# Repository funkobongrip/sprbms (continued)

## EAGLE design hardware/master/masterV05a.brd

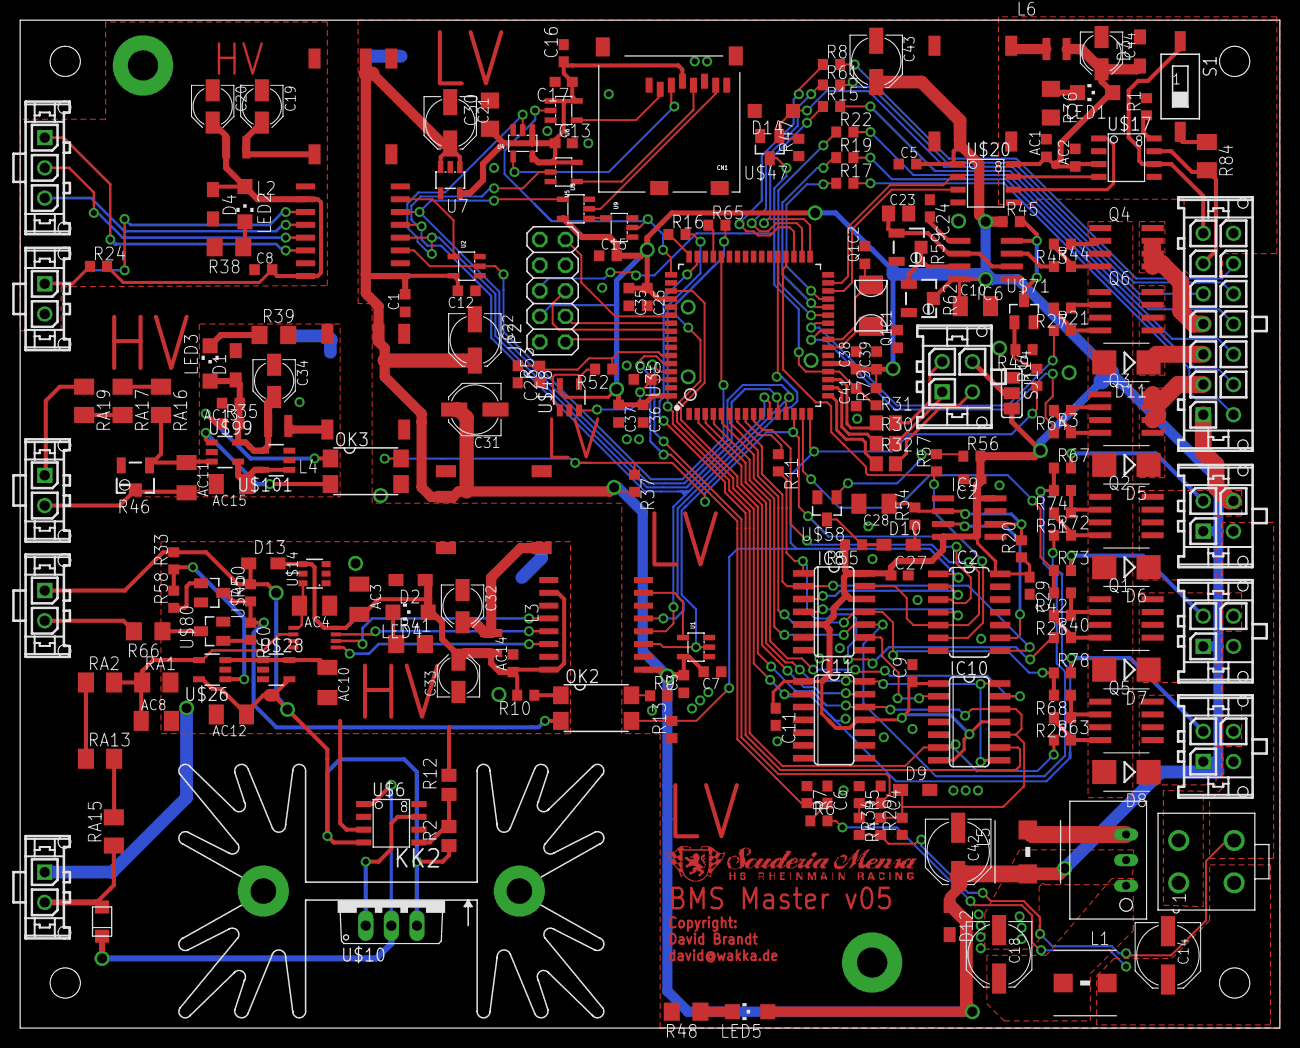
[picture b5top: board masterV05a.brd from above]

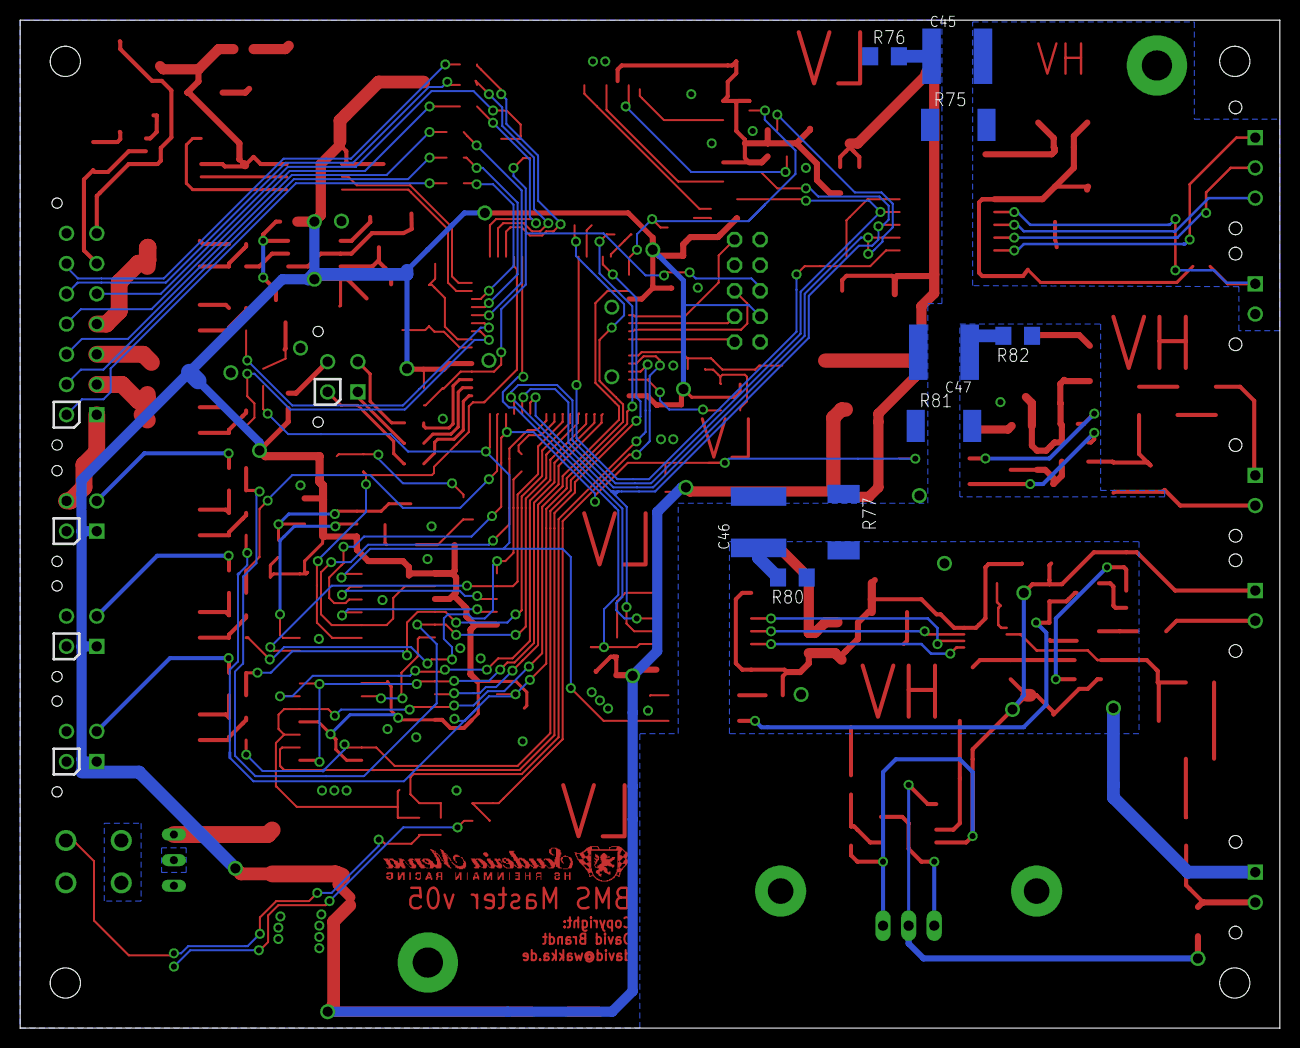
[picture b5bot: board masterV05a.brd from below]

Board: 2 copper layers, 125.0 x 100.0 mm, 234 parts (9 on the bottom side), 162 nets.

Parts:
AC1, AC2, AC13, AC14: 100n; C0603K
AC3: 1u; C1206K
AC4, AC8, AC10, AC11, AC12, AC15: 10u; C1206K
C1, C3, C5, C7, C8, C12, C15, C25, C36, C38, C41: 100n; C0603K
C2, C4, C6, C9, C11, C26, C27, C29: 1u; C0603
C10: 10u; C1206K
C13, C16, C17: 100n; C0603
C14, C18: 22u50v; PANASONIC_D
C19, C20, C32, C33, C34, C44: 10u16V; PANASONIC_B
C21, C22, C31, C43: 33u10V; PANASONIC_C
C23: 1u; C0805K
C24: 10n; C0603
C28: 2.2u; C1206K
C30: 10u; C1206
C35, C37, C39, C40: 1u; C0603K
C42: 150u10v; PANASONIC_D
C45: DNP; C2220K
C46, C47: C2220K
CN1: MICROSD
D1, D2, D3, D4, D12: 5.5; SOD323-W
D5, D6, D7, D8, D11: SMB
D9: 5.1; SOD323-W
D10, D13: SOD323-W
D14: 20V; SOD123
D15: RS07J; DO-219AB
DC2, DC3, DC4, DC5: TES 1-0511; ISF
IC2: 74AC04D; SO14
IC6, IC9: NE555D; SO08
IC8: 4082D; SO14
IC10, IC11: 74AC11074D; SO14
JP2: 2X05
KK2: SK129-PAD; SK129
L1, L5: 7447786008; WE-PD_6033/6050_PLASTIC_BASE
L2, L3, L4, L6: 74479887310; WE-PMI_1008
LED1, LED2, LED3, LED4, LED5: 1318255; CHIPLED_1206
OK2, OK3: LTV816S; SMD4
Q1, Q2, Q3, Q4, Q5, Q6: SO-08
Q1C1, Q1C2: 18pf; C0603K
R1: 1.5k; R0603
R2, R12: R0805
R3, R21, R40, R44, R63, R72: 10; R0603
R4, R6: 4.7k; R0603
R5, R7: 680; R0603
R8, R15, R17, R19, R22, R24, R42, R45, R52, R57, R58, R60, R61, R68: 1k; R0603
R9, R47, R54, R67, R73, R78: 100; R0603
R10, R35: 330; R0603
R11, R16, R20, R49, R55, R56, R65: 100k; R0603
R13, R14, R29, R33, R34, R37, R50, R74, R79: 10k; R0603
R26, R27, R28, R43, R51, R64: 470; R0603
R30, R31, R32: 220; R0805
R36, R38, R39, R41, R48: 140; R1206
R46: 100k; 3223W
R53: NTC1k; R0603
R59: 500k; 3223W
R62: 5k; 3223W
R66: 470; R1206
R75: DNP; R2512
R76: DNP; R1206
R77, R81: R2512
R80, R82: R1206
R84: 120; M1206
RA1: 10k; M1206
RA2, RA13, RA15, RA16, RA17, RA19: 330k; M1206
S1: SWS001; SMS-001
SJ1: SJ_2
U1, U2, U9: SOT23-5
U3: AT90CAN128-16AI; TQFP64-0.8MM
U4, U5, U6, U8: SN74AHC1G126DBVR; SOT23-5
U7: LP2985-33DBVR; SOT23-DBV
U$6: LR645; SO-8
U$9: ADUM1401; SO16WB
U$10: DN2540TO220; TO220V
U$11: ADUM1301; SO16WB
U$14: LT6656; SOT23-6
U$16: LTC1864; MS8
U$17: MCP2551; SO-8
U$20: ADUM1201; SO-8
U$26, U$99: LT1716; SOT23-5
U$28, U$101: LT6650; SOT23-5
U$45, U$47, U$58, U$71, U$80: 2N7002; SOT23
U$48: LT1782; SOT23-5
U$50: TSR1
U$1000: SMLOGOS
X1, X2, X9, X13: 43650-0215
X3: 43045-1412
X4, X5, X6, X8: 43045-0412
X7: 43650-0315
X10: MINI-FIT-JR-045566; 5566-04
Y1: 16Mhz; CX-53G

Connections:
40VOUT: OK2.2, R50.1, R60.1, U$45.3
!40VCOUT: R66.1, U$80.3
!40VCOUTW: R33.1, R58.2, U$26.1
!ANDOUT2: D10.C, R55.1, U$58.3
!CSADC: U1.2, U3.37, U$11.P$3
!CSLT: U2.2, U3.44, U$9.P$3
!PRECH_C: IC2.3, OK3.4, R37.1, U3.14
!RELAI+_C: IC2.6, R57.1, U3.36
!RELAI+_CC: IC2.9, IC9.3
!RESET: C41.2, JP2.6, R79.1, U3.20, U$47.3
!SDCS: U3.49, U6.2, U9.2
!SDCS3: CN1.2, U6.4
+3V3: C13.1, C16.1, C17.1, C30.1, CN1.4, U4.1, U4.5, U5.1, U5.5, U6.1, U6.5, U7.5
+5V: C1.2, C2.1, C3.2, C5.2, C7.2, C9.1, C10.1, C11.1, C12.2, C15.2, C21.+, C22.+, C25.1, C27.1, C29.1, C31.+, C35.1, C36.1, C37.1, C38.1, C39.1, C42.+, C43.+, D12.C, DC2.2, DC3.2, DC4.2, DC5.2, IC2.14, IC6.8, IC8.5, IC8.12, IC8.14, IC9.4, IC9.8, IC10.1, IC10.7, IC10.11, IC11.1, IC11.11, JP2.4, L5.2, LED5.A, R9.2, R20.1, R37.2, R45.1, R55.2, R56.2, R62.2, R79.2, SJ1.3, U1.5, U2.5, U3.21, U3.52, U3.64, U7.1, U7.3, U8.5, U9.5, U$9.P$1, U$11.P$1, U$20.1, U$48.5, X4.1, X5.1, X6.1
+5VL: L5.1, U$50.3
ANDOUTD: D10.A, R54.1
AREF: C40.2, U3.62, U$48.3
AREFP: R52.2, U$48.1, U$48.4
AVREF3: AC15.1, U$99.4, U$101.1, U$101.5
AVREF400MV: AC10.1, U$26.3, U$28.1, U$28.5
B40V: IC2.2, IC8.3
B!40V: IC2.1, OK2.3, R13.2, R14.1, U3.16
B!40VE: OK2.4, R9.1
B+5V: AC3.2, AC14.1, C33.+, D2.C, D13.A, L3.2, LED4.A, R10.2, U$11.P$10, U$11.P$16, U$14.4, U$16.P$8
B+5VL: C32.+, DC5.5, L3.1
B+12V: AC12.1, D13.C, R2.1, R33.2, R50.2, U$6.4, U$10.3, U$26.5, U$28.4, X2.1
BACONV: U$11.P$14, U$16.P$5
BASCK: U$11.P$13, U$16.P$7
BASDO: U$11.P$12, U$16.P$6
BAT: D15.A, RA15.1, X1.2
BATD: D15.C, U$6.1, U$10.2
BATM: AC8.1, RA1.1, RA2.2, U$16.P$2, U$26.4
BATM1: RA2.1, RA13.1
BATM3: RA13.2, RA15.2
BGND: AC3.1, AC4.1, AC8.2, AC10.2, AC12.2, AC14.2, C32.-, C33.-, D2.A, DC5.4, R12.2, R41.2, R77.2, R80.1, RA1.2, U$6.3, U$11.P$9, U$11.P$15, U$14.1, U$14.2, U$16.P$3, U$16.P$4, U$26.2, U$28.2, U$45.2, U$80.2, X1.1
BMSRESET: D14.C, R47.2, U$47.1, X3.5
C1RS: R1.1, U$17.8
CAN+5V: AC1.1, AC2.1, C44.+, D3.C, L6.2, LED1.A, U$17.3, U$20.8
CAN+5VL: DC2.5, L6.1
CANGND: AC1.2, AC2.2, C44.-, D3.A, DC2.4, R1.2, R36.2, U$17.2, U$20.5, X3.14
CANH: R84.2, U$17.7, X3.6
CANL: S1.1, U$17.6, X3.7
CANM: R84.1, S1.2
CAN_RX: U3.31, U$20.2
CAN_TX: U3.30, U$20.3
CM+5V: AC13.1, C34.+, D1.C, L4.2, LED3.A, R35.2, U$99.5, U$101.4
CM+5VL: DC4.5, L4.1
CMGND: AC11.2, AC13.2, AC15.2, C34.-, D1.A, DC4.4, R39.2, R46.2, R81.2, R82.1, U$99.2, U$101.2, X9.2
CSADC: U1.4, U$11.P$7
CSLT: U2.4, U$9.P$7
CURR: RA19.1, X9.1
CURRM: AC11.1, R46.1, RA16.2, U$99.3
CURRM4: RA16.1, RA17.1
CURRM7: RA17.2, RA19.2
DISCHARGE: D6.C, Q2.5, Q2.6, Q2.7, Q2.8, X3.1, X6.4
FFCLK: IC10.8, IC10.14, IC11.14, U3.3
GND: C1.1, C2.2, C3.1, C4.1, C5.1, C6.1, C7.1, C9.2, C10.2, C11.2, C12.1, C13.2, C14.-, C15.1, C16.2, C17.2, C18.-, C21.-, C22.-, C23.2, C24.1, C25.2, C26.2, C27.2, C28.2, C29.2, C30.2, C31.-, C35.2, C36.2, C37.2, C38.2, C39.2, C40.1, C41.1, C42.-, C43.-, C46.2, C47.2, CN1.6, CN1.MT1, CN1.MT2, D5.A, D6.A, D7.A, D8.A, D9.A, D11.A, D12.A, D14.A, DC2.1, DC3.1, DC4.1, DC5.1, IC2.7, IC6.1, IC8.7, IC9.1, IC10.4, IC11.4, JP2.2, JP2.10, OK3.3, Q1.1, Q1.2, Q1.3, Q1C1.1, Q1C2.2, Q2.1, Q2.2, Q2.3, Q3.1, Q3.2, Q3.3, Q4.1, Q4.2, Q4.3, Q5.1, Q5.2, Q5.3, Q6.1, Q6.2, Q6.3, R5.1, R7.1, R13.1, R26.1, R27.1, R28.1, R29.1, R42.1, R43.1, R47.1, R48.2, R49.1, R51.1, R53.1, R64.1, R68.1, R74.1, R75.1, R76.1, R77.1, R81.1, SJ1.1, U1.3, U2.3, U3.22, U3.53, U3.63, U4.3, U5.3, U6.3, U7.2, U8.3, U9.3, U$9.P$2, U$9.P$8, U$11.P$2, U$11.P$8, U$20.4, U$47.2, U$48.2, U$50.2, U$58.2, U$71.2, X10.P1, X10.P2
GPIO1: R17.2, X3.8
GPIO2/TX: R19.2, X3.9
GPIO3/RX: R22.2, X3.10
GPIO4: R15.2, X3.11
GPIO5: R61.2, X3.12
GPIO6: R8.2, X3.13
GPOC1: D5.C, Q3.5, Q3.6, Q3.7, Q3.8, X3.2
GPOC2: D11.C, Q6.5, Q6.6, Q6.7, Q6.8, X3.3
ISO_CAN_RX: U$17.4, U$20.7
ISO_CAN_TX: U$17.1, U$20.6
LR645_G: U$6.7, U$10.1
LR645_TRIM: R2.2, R12.1, U$6.5
MISO: U3.13, U8.4, U$9.P$6, U$11.P$5
MISO3: CN1.7, U8.2
MOSI: U3.12, U4.2, U$9.P$4
MOSI3: CN1.3, U4.4
unnamed: R58.1, U$45.1
unnamed: R60.2, U$80.1
unnamed: R66.2, X2.2
NE555_TR: C28.1, IC9.2, IC9.6, R20.2, R54.2
OK2A: OK2.1, R10.1
OPTOLED: OK3.1, R35.1
OSC1: Q1C2.1, U3.24, Y1.P$2
OSC2: Q1C1.2, U3.23, Y1.P$1
PLEDC1: LED1.C, R36.1
PLEDC2: LED2.C, R38.1
PLEDC3: LED3.C, R39.1
PLEDC4: LED4.C, R41.1
PLEDC5: LED5.C, R48.1
PRECHARGEOPTO: OK3.2, U$99.1
PRECH_C: IC2.4, IC8.4
REF-4.096: AC4.2, U$14.6, U$16.P$1
RELAI+: IC8.1, R11.2, R40.1
RELAI+12V: R4.2, R34.1, X4.3, X5.3, X6.3, X10.P4
RELAI+CLOSED: R42.2, R73.1, U3.15
RELAI+FF: IC8.9, IC10.2
RELAI+G: Q1.4, R26.2, R40.2
RELAI+GND: D7.C, Q1.5, Q1.6, Q1.7, Q1.8, X5.4
RELAI+S: R11.1, U3.8
RELAI+_AND: IC2.5, IC8.13, U3.9
RELAI+_CG: R56.1, R57.2, U$58.1
RELAI+_CLOSED_AP: R73.2, X5.2
RELAI+_DELAYED: IC2.8, IC8.2, U3.7
RELAI-: IC10.6, R16.2, R63.1
RELAI-CLOSED: IC8.11, R68.2, R78.1, U3.6
RELAI-G: Q5.4, R28.2, R63.2
RELAI-GND: D8.C, Q5.5, Q5.6, Q5.7, Q5.8, X4.4
RELAI-R: R16.1, U3.48
RELAI-_CLOSED_AP: R78.2, X4.2
RELAIPDG: Q2.4, R51.2, R72.2
RELAIPDG1: Q3.4, R3.2, R64.2
RELAIPDG2: Q6.4, R21.2, R27.2
RELAIPD_CLOSED_AP: R67.2, X6.2
RELAI_PD: IC11.2, R65.2, R72.1
RELAI_PDCLOSED: IC8.10, R67.1, R74.2, U3.5
RELAI_PDR: R65.1, U3.45
RELAI_VCC5: D9.C, IC10.10, IC10.12, IC11.12, R29.2, R34.2, U3.51
RELAI_VCC_SENS: C4.2, R4.1, R5.2, U3.61
S!CSLT: U$9.P$14, X7.1
S+5V: C8.2, C20.+, D4.C, L2.2, LED2.A, R24.2, U$9.P$10, U$9.P$16
S+5VL: C19.+, DC3.5, L2.1
SCK: U3.11, U5.2, U$9.P$5, U$11.P$4
SCK3: CN1.5, U5.4
SDCS: U8.1, U9.4
SGND: C8.1, C19.-, C20.-, C45.2, D4.A, DC3.4, R38.2, R75.2, U$9.P$9, U$9.P$15, X13.2
SGNDGND: C45.1, R76.2
SGNDGND1: C46.1, R80.2
SGNDGND2: C47.1, R82.2
SLEDB: R32.2, X8.3
SLEDG: R31.2, X8.2
SLEDPOW: SJ1.2, X8.4
SLEDR: R30.2, X8.1
SMISO: R24.1, U$9.P$11, X13.1
SMOSI: U$9.P$13, X7.2
SSCK: U$9.P$12, X7.3
TCK: JP2.1, U3.57
TDI: JP2.9, U3.54
TDO: JP2.3, U3.55
TEMPM: C26.1, R52.1, R53.2, U3.59
TMS: JP2.5, U3.56
TSAL: Q4.5, Q4.6, Q4.7, Q4.8, X3.4
TSAL!R: IC6.4, R45.2, U$71.3
TSALCV: C24.2, IC6.5
TSALDIS: IC6.7, R59.2, R62.1
TSALG: Q4.4, R43.2, R44.2
TSALGOUT: R14.2, R49.2, U$71.1
TSALPR: C23.1, IC6.2, IC6.6, R59.1
TSALQ: IC6.3, R44.1
UC_GPIO1: R17.1, U3.29
UC_GPIO2: R19.1, U3.28
UC_GPIO3: R22.1, U3.27
UC_GPIO4: R15.1, U3.33
UC_GPIO5: R61.1, U3.34
UC_GPIO6: R8.1, U3.35
UC_GPOC1: R3.1, U3.25
UC_GPOC2: R21.1, U3.26
UC_RELAI+: IC10.13, U3.4
UC_RELAI-: IC10.9, U3.47
UC_RELAI_PD: IC11.13, U3.2
UC_SLEDB: R32.1, U3.17
UC_SLEDG: R31.1, U3.19
UC_SLEDR: R30.1, U3.18
VCC: C14.+, L1.1, R6.2, X10.P3
VCC2: C18.+, L1.2, U$50.1
VCC_SENS: C6.2, R6.1, R7.2, U3.60

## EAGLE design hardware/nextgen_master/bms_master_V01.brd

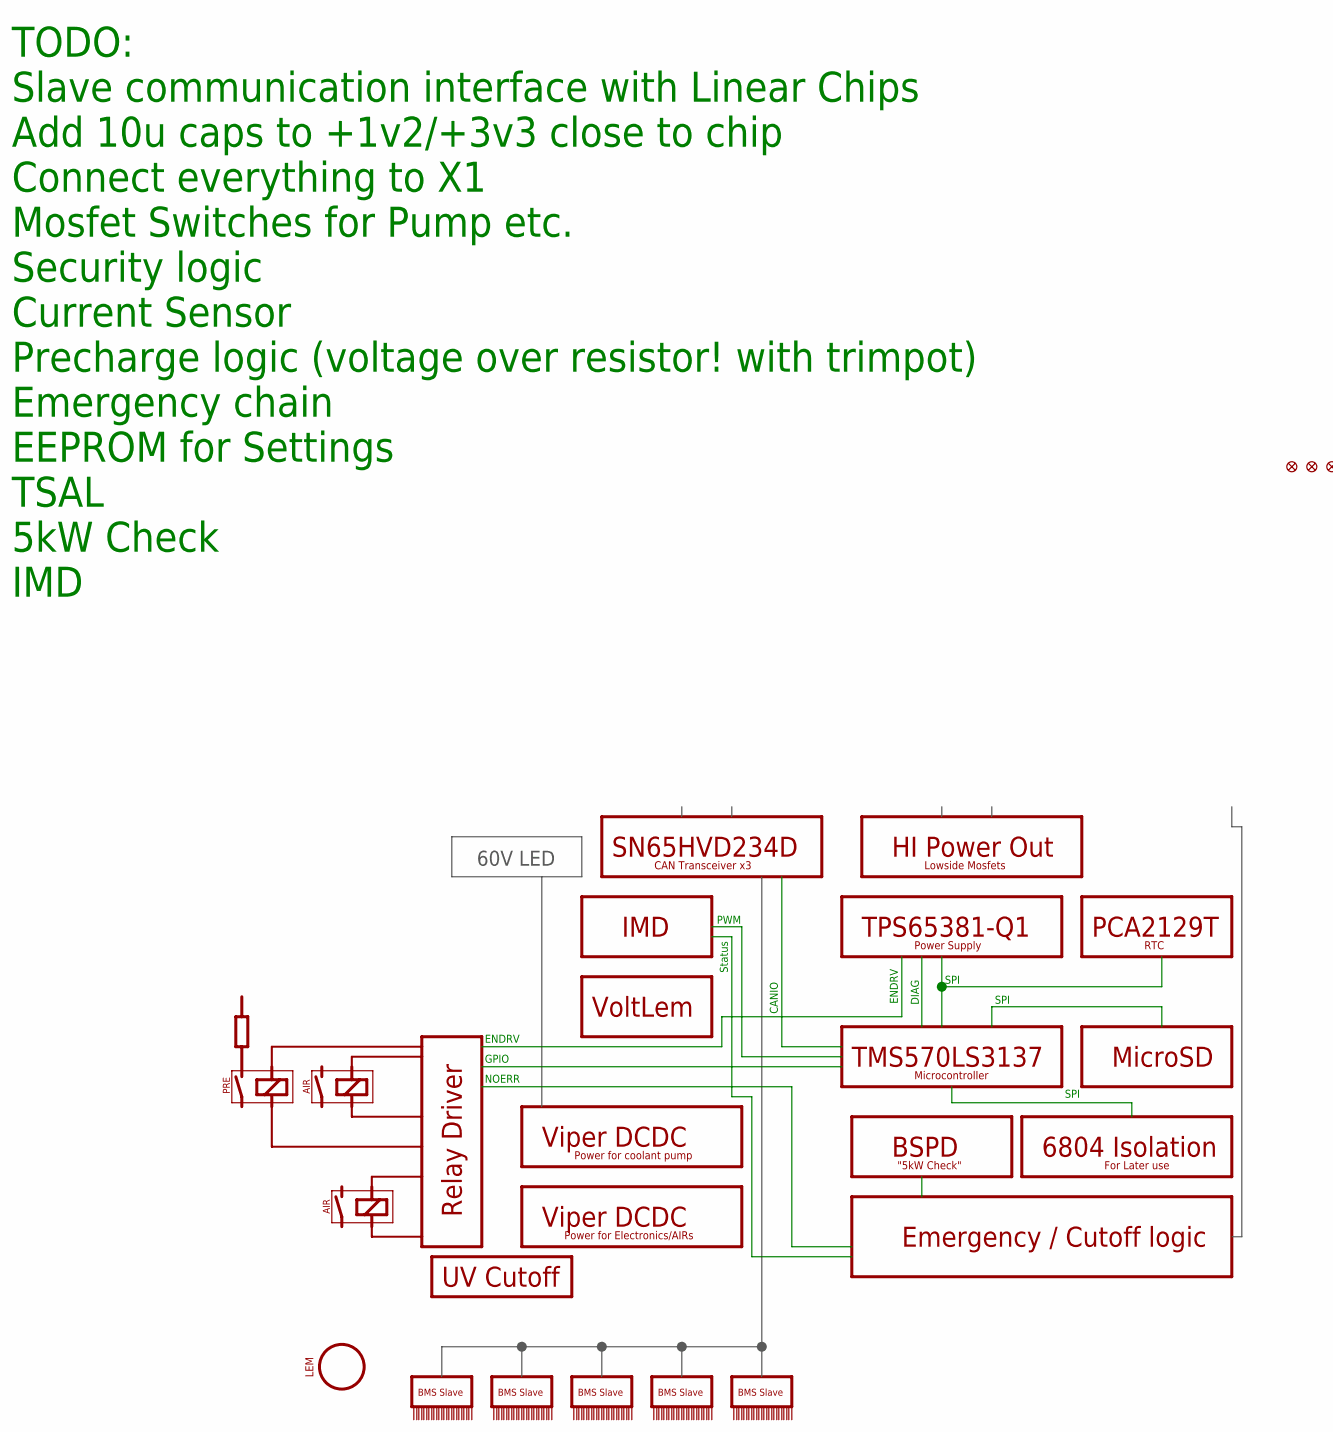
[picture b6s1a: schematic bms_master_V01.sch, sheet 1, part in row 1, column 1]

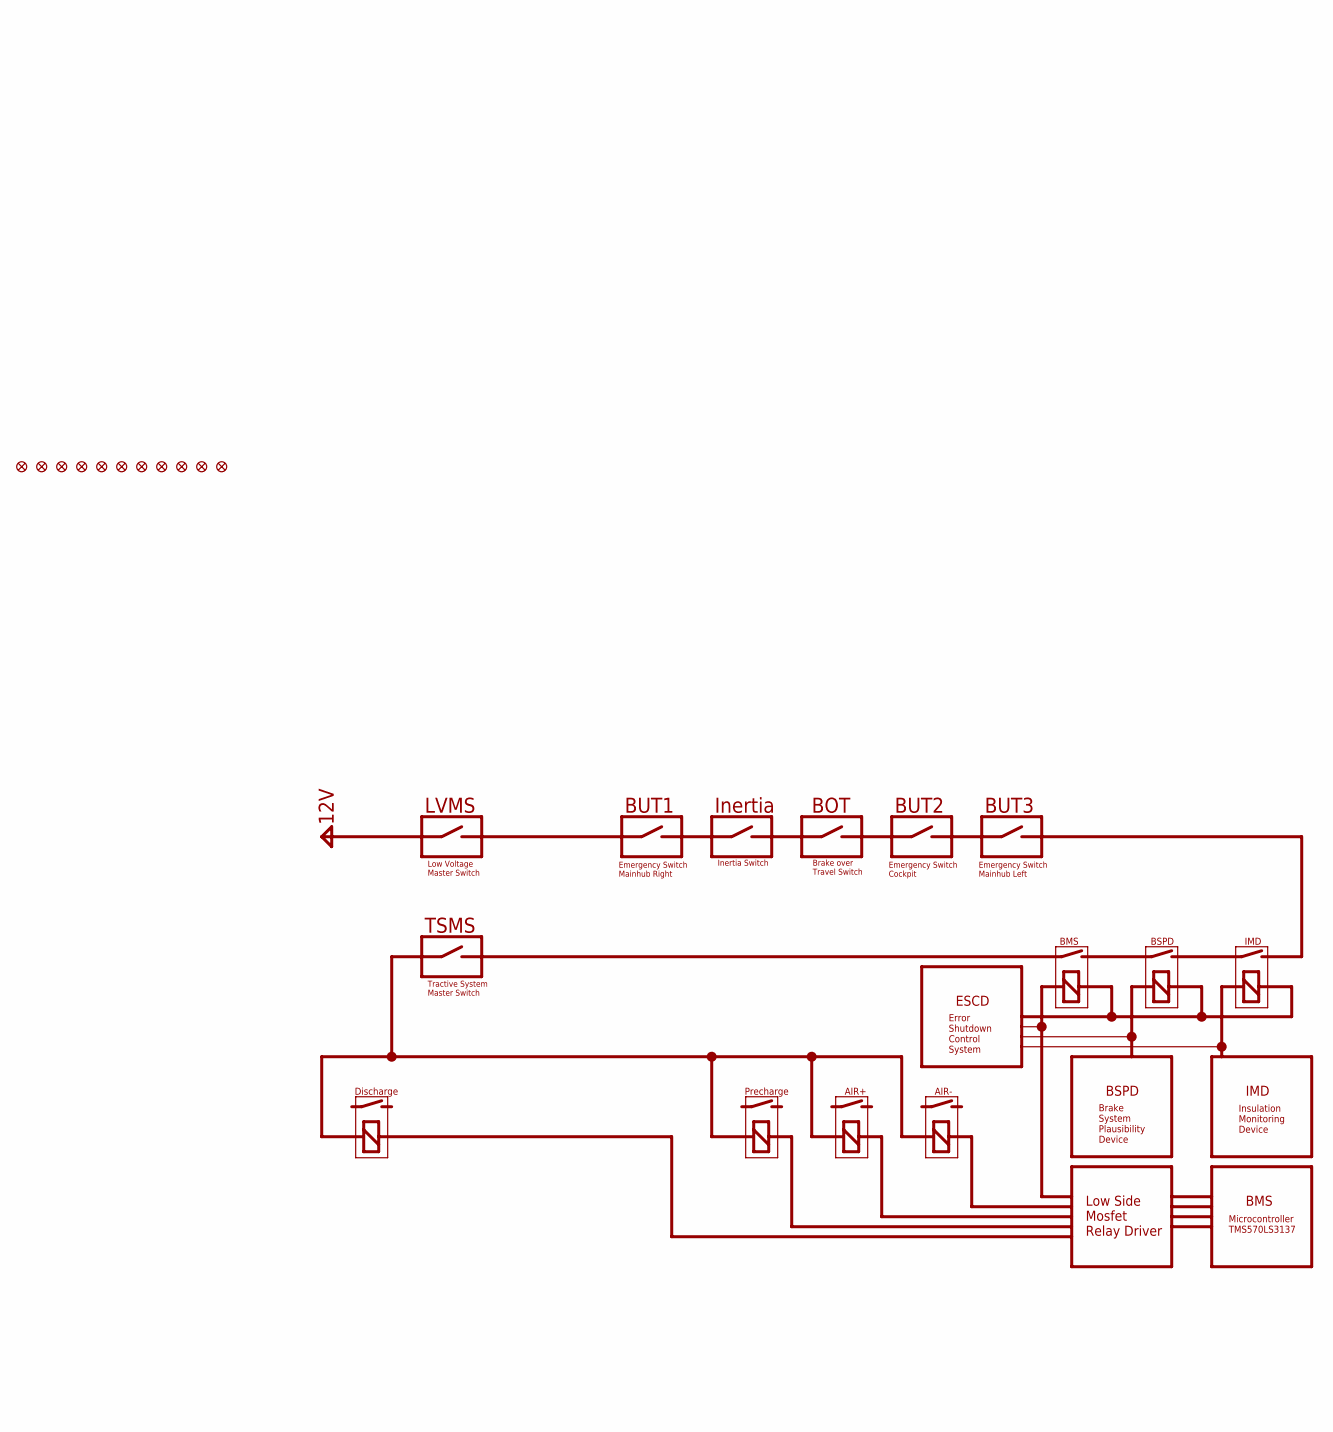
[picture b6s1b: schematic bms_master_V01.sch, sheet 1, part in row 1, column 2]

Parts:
FID1, FID2, FID3, FID4, FID5, FID6, FID7, FID8, FID9, FID10, FID11: FIDUCIAL""; FIDUCIAL_1MM

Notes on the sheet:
TODO: Slave communication interface with Linear Chips Add 10u caps to +1v2/+3v3 close to chip Connect everything to X1 Mosfet Switches for Pump etc. Security logic Current Sensor Precharge logic (voltage over resistor! with trimpot) Emergency chain EEPROM for Settings TSAL 5kW Check IMD
TMS570LS3137
TPS65381-Q1
Power Supply
Microcontroller
PCA2129T
RTC
SPI
DIAG
MicroSD
SN65HVD234D
CAN Transceiver x3
CANIO
BMS Slave
6804 Isolation
For Later use
AIR
PRE
Relay Driver
GPIO
ENDRV
BSPD
LEM
NOERR
Viper DCDC
Power for coolant pump
Power for Electronics/AIRs
VoltLem
UV Cutoff
HI Power Out
Lowside Mosfets
Emergency / Cutoff logic
IMD
PWM
Status
60V LED
"5kW Check"
LVMS
Inertia
BOT

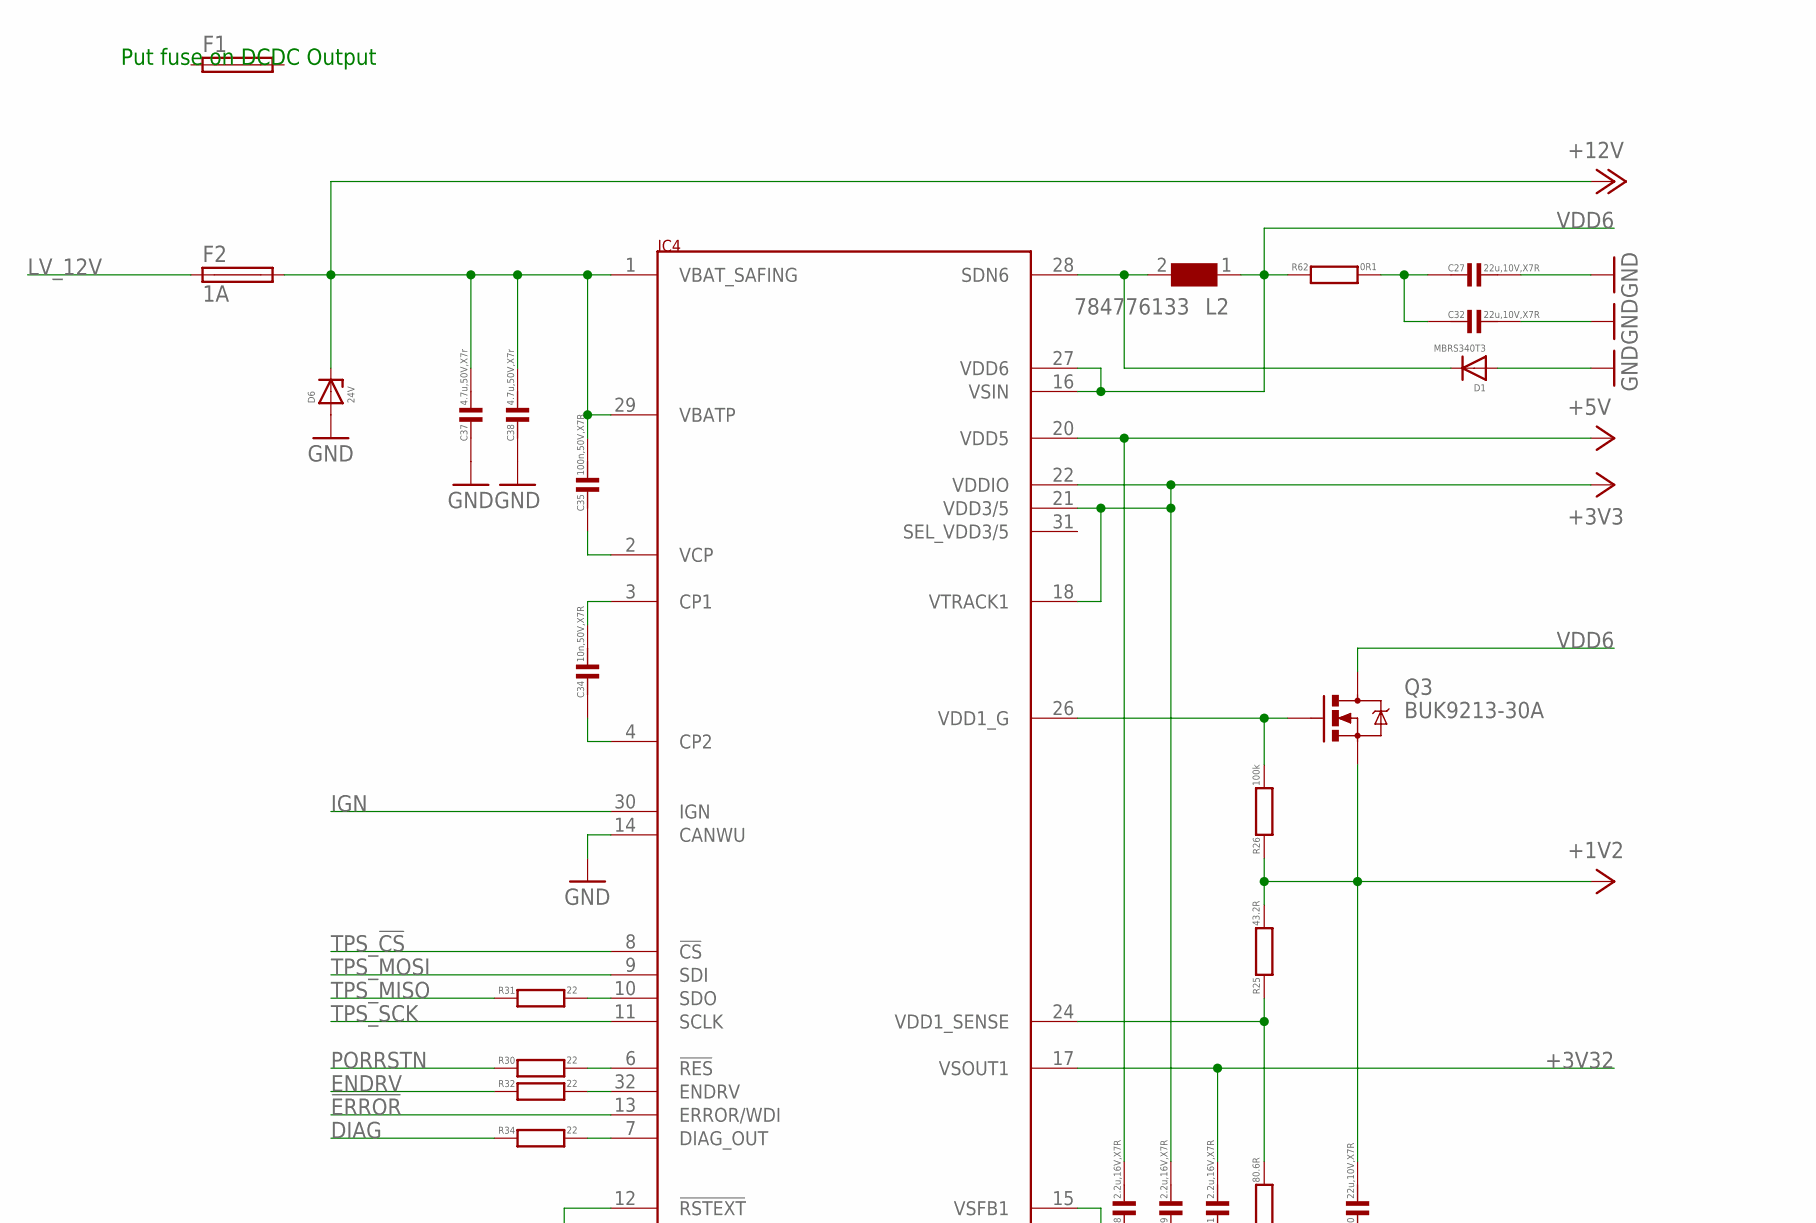
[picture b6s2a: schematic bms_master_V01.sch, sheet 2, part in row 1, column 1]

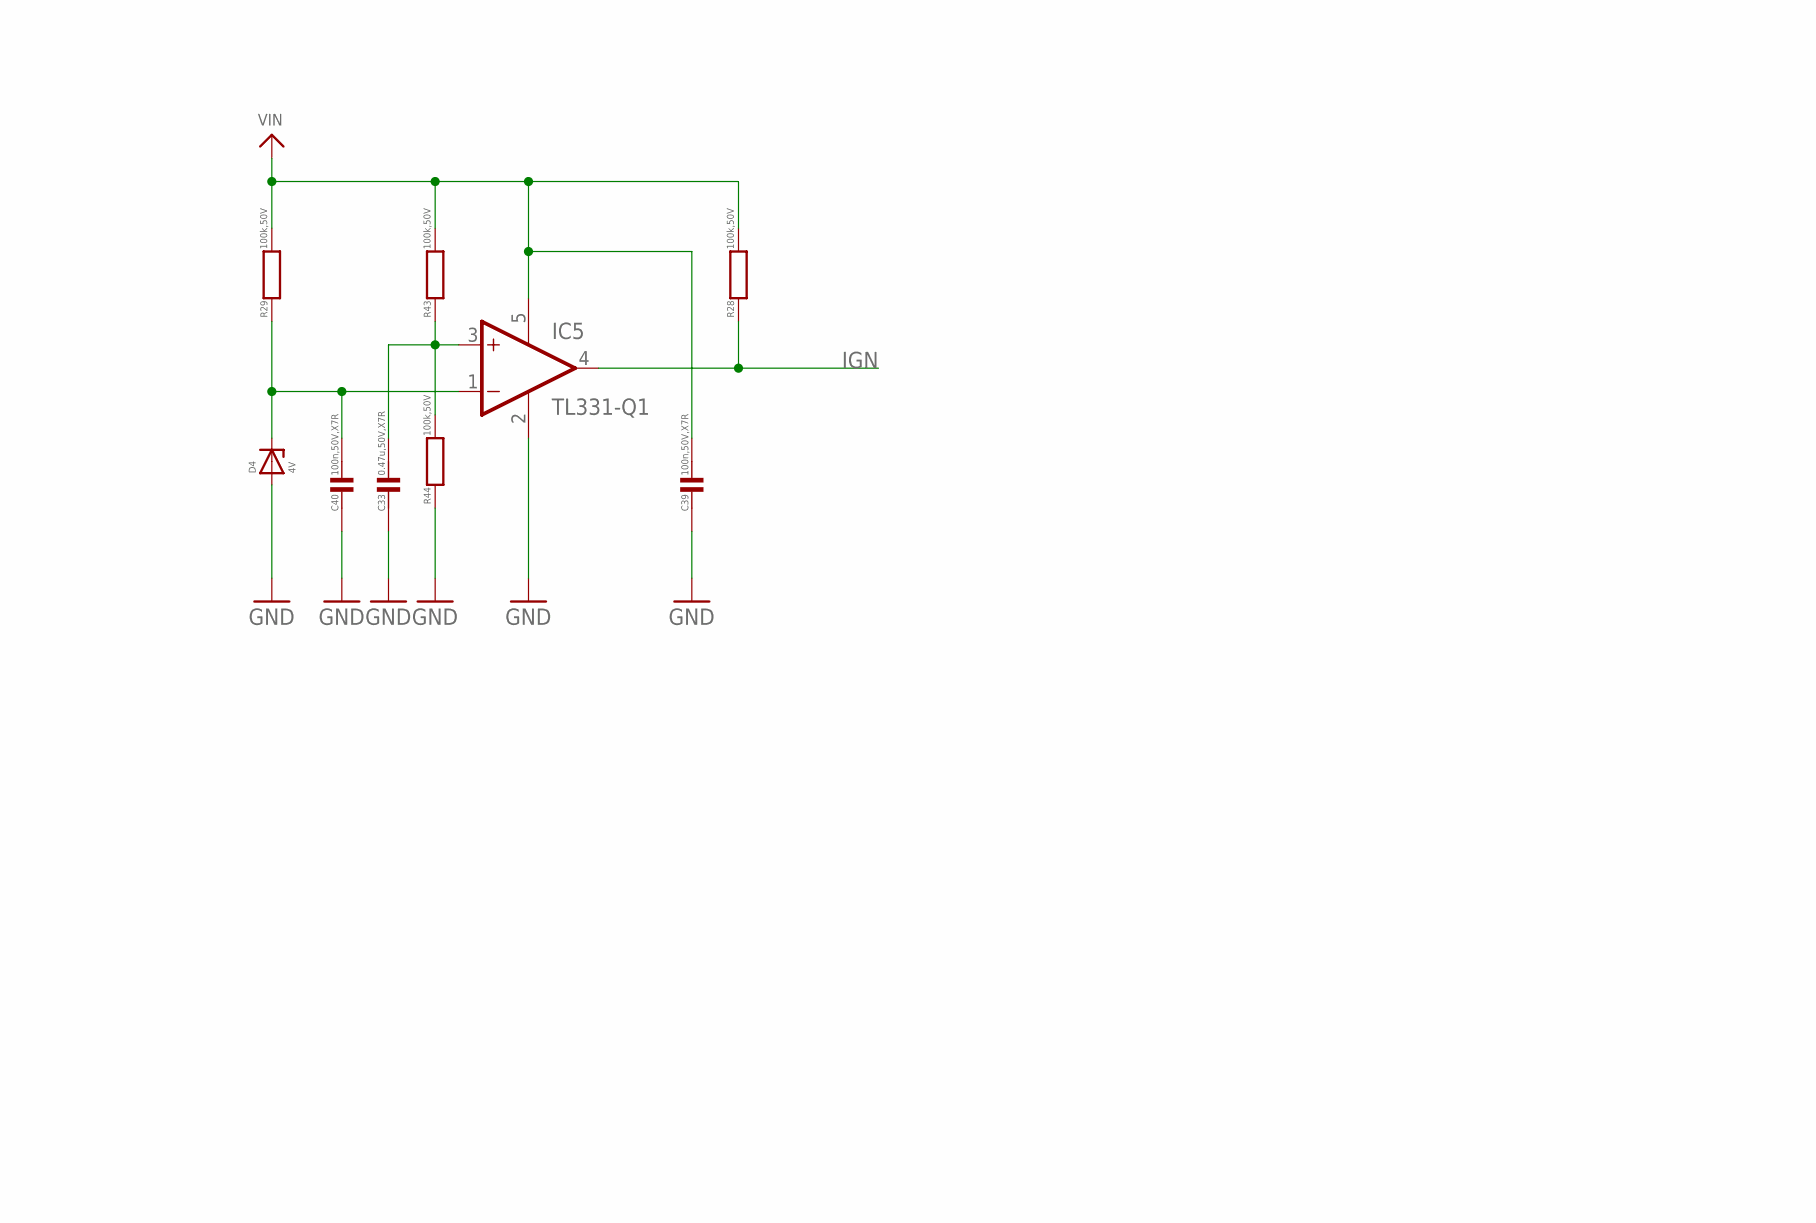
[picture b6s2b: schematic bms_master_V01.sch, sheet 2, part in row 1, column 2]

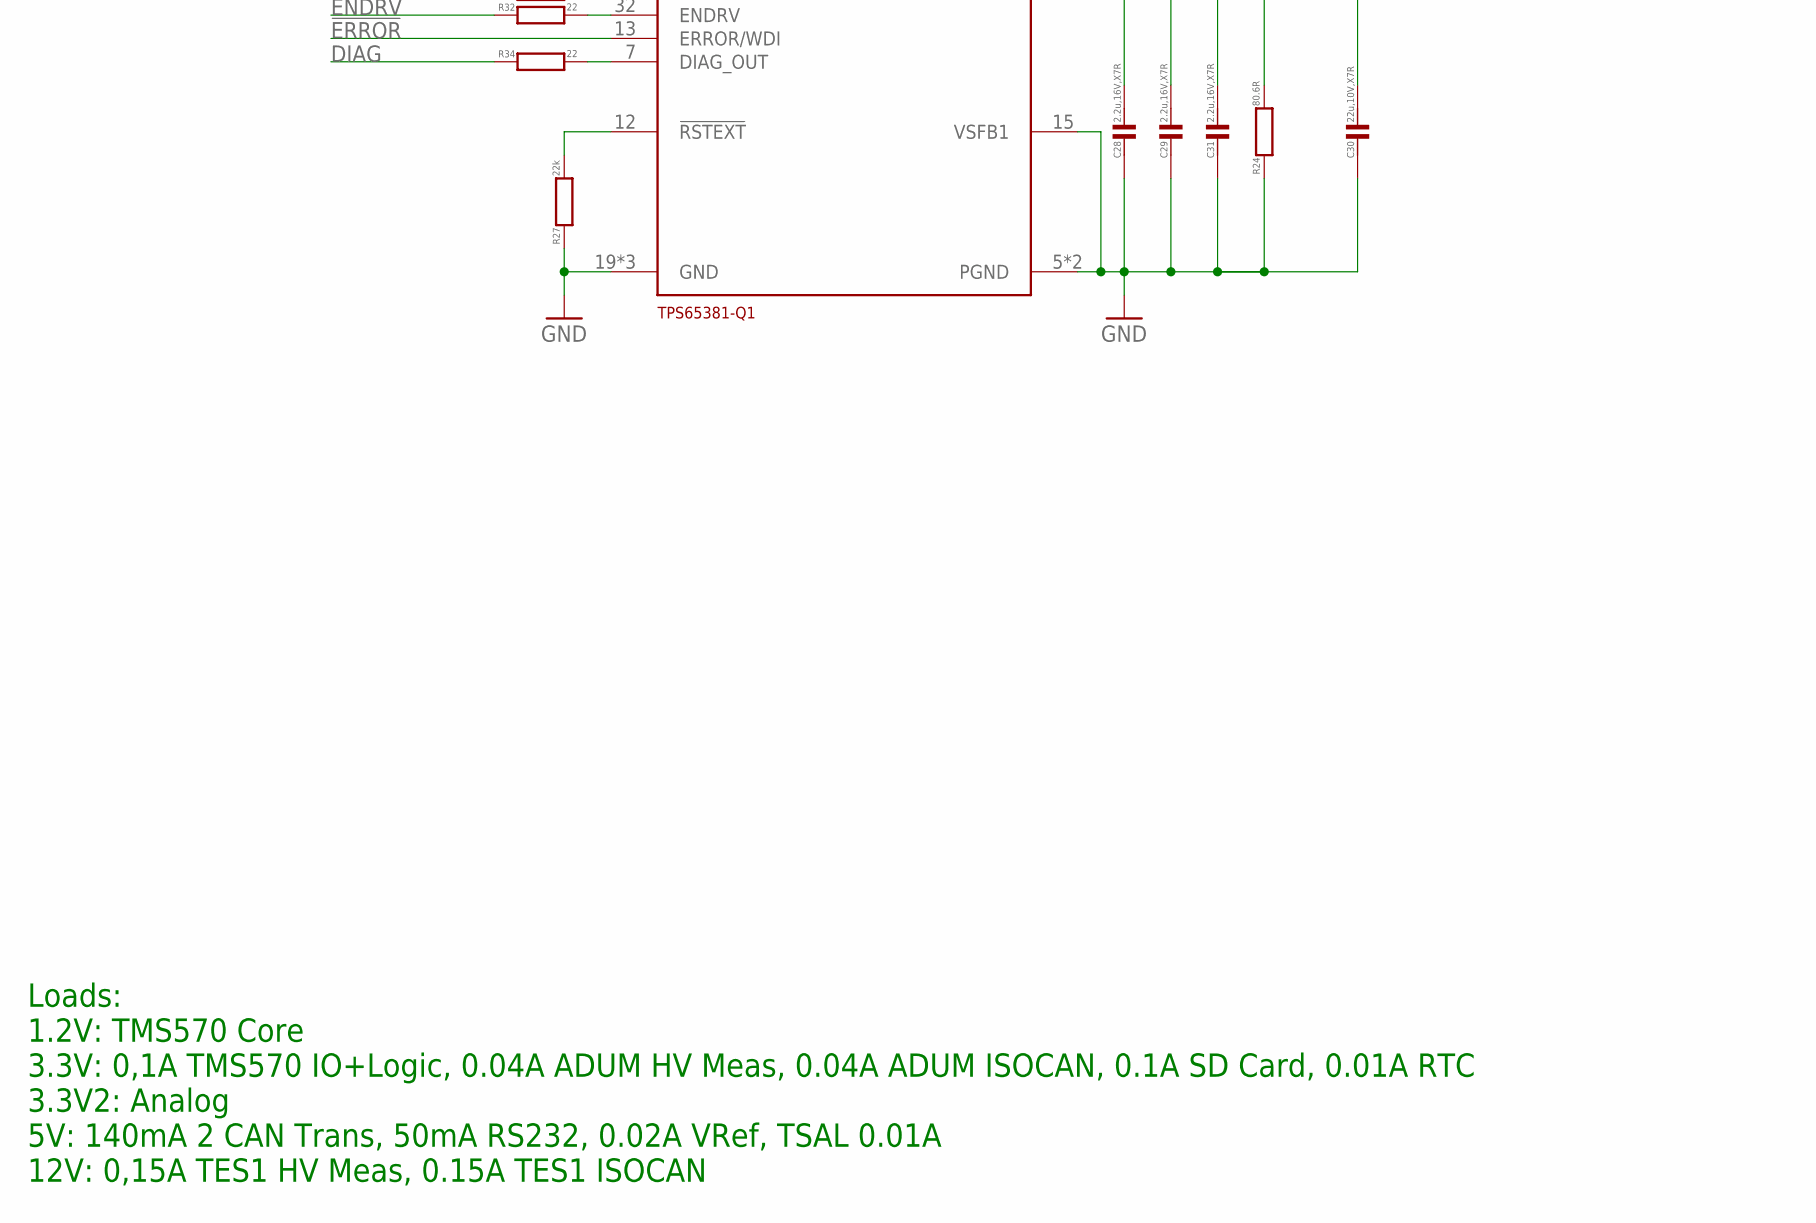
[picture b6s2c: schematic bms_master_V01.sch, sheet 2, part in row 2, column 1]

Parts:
C27, C30, C32: 22u,10V,X7R; C1206
C28, C29, C31: 2.2u,16V,X7R; C0603
C33: 0.47u,50V,X7R; C0603
C34: 10n,50V,X7R; C0603
C35, C39, C40: 100n,50V,X7R; C0603
C37, C38: 4.7u,50V,X7r; C1210
D1: MBRS340T3; SMC
D4: 4V; SOD323-L
D6: 24V; SMB
F1: FUSE-LFMINIHOLDER; LITTLEFUSE_17867640001
F2: 1A; LITTLEFUSE_17867640001
IC4: TPS65381-Q1; DAP-R-PDSO-G32
IC5: TL331-Q1; DBV-R-PDSO-G5
L2: 784776133; WE-PD2_1054
Q3: BUK9213-30A; DPAK
R24: 80.6R; R0603
R25: 43.2R; R0603
R26: 100k; R0402
R27: 22k; R0402
R28, R29, R43, R44: 100k,50V; R0603
R30, R31, R32, R34: 22; R0402
R62: 0R1; R1206

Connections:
8VREF: C40.1, D4.C, IC5.1 (-IN), R29.1
!ERROR: IC4.13 (ERROR/WDI); also elsewhere on the board
+1V2: C30.1, Q3.3 (S), R25.2, R26.1; also elsewhere on the board
+3V3: C29.1, IC4.18 (VTRACK1), IC4.21 (VDD3/5), IC4.22 (VDDIO); also elsewhere on the board
+3V32: C31.1, IC4.17 (VSOUT1); also elsewhere on the board
+5V: C28.1, IC4.20 (VDD5); also elsewhere on the board
+12V: C35.1, C37.1, C38.1, D6.C, F2.2, IC4.1 (VBAT_SAFING), IC4.29 (VBATP); also elsewhere on the board
CP1: C34.1, IC4.3 (CP1)
CP2: C34.2, IC4.4 (CP2)
DIAG: R34.1; also elsewhere on the board
DIAG_OUT: IC4.7 (DIAG_OUT), R34.2
ENDRV: R32.1; also elsewhere on the board
ENDRVOUT: IC4.32 (ENDRV), R32.2
GND: C27.1, C28.2, C29.2, C30.2, C31.2, C32.1, C33.2, C37.2, C38.2, C39.2, C40.2, D1.A, D4.A, D6.A, IC4.5 (PGND), IC4.14 (CANWU), IC4.15 (VSFB1), IC4.19 (GND), IC4.23 (GND), IC4.25 (PGND), IC4.P (GND), IC5.2 (GND), R24.1, R27.1, R44.1; also elsewhere on the board
IGN: IC4.30 (IGN), IC5.4 (OUT), R28.1
LV_12V: F2.1; also elsewhere on the board
unnamed: C33.1, IC5.3 (+IN), R43.1, R44.2
unnamed: C27.2, C32.2, R62.2
unnamed: D1.C, IC4.28 (SDN6), L2.2
PORRSTN: R30.1; also elsewhere on the board
PORRSTOUT: IC4.6 (!RES), R30.2
RSTEXT: IC4.12 (!RSTEXT), R27.2
SDO: IC4.10 (SDO), R31.2
TPS_!CS: IC4.8 (!CS); also elsewhere on the board
TPS_MISO: R31.1; also elsewhere on the board
TPS_MOSI: IC4.9 (SDI); also elsewhere on the board
TPS_SCK: IC4.11 (SCLK); also elsewhere on the board
VCP: C35.2, IC4.2 (VCP)
VDD1_G: IC4.26 (VDD1_G), Q3.1 (G), R26.2
VDD1_SENSE: IC4.24 (VDD1_SENSE), R24.2, R25.1
VDD6: IC4.16 (VSIN), IC4.27 (VDD6), L2.1, Q3.4 (D), R62.1
VIN: C39.1, IC5.5 (V+), R28.2, R29.2, R43.2; also elsewhere on the board

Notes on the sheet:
Put fuse on DCDC Output
Loads: 1.2V: TMS570 Core 3.3V: 0,1A TMS570 IO+Logic, 0.04A ADUM HV Meas, 0.04A ADUM ISOCAN, 0.1A SD Card, 0.01A RTC 3.3V2: Analog 5V: 140mA 2 CAN Trans, 50mA RS232, 0.02A VRef, TSAL 0.01A 12V: 0,15A TES1 HV Meas, 0.15A TES1 ISOCAN
SPI, !ERROR!, DIAG, RST to uC, ENDRV to Security
1.2V, 3.3V, 5V, 12V
